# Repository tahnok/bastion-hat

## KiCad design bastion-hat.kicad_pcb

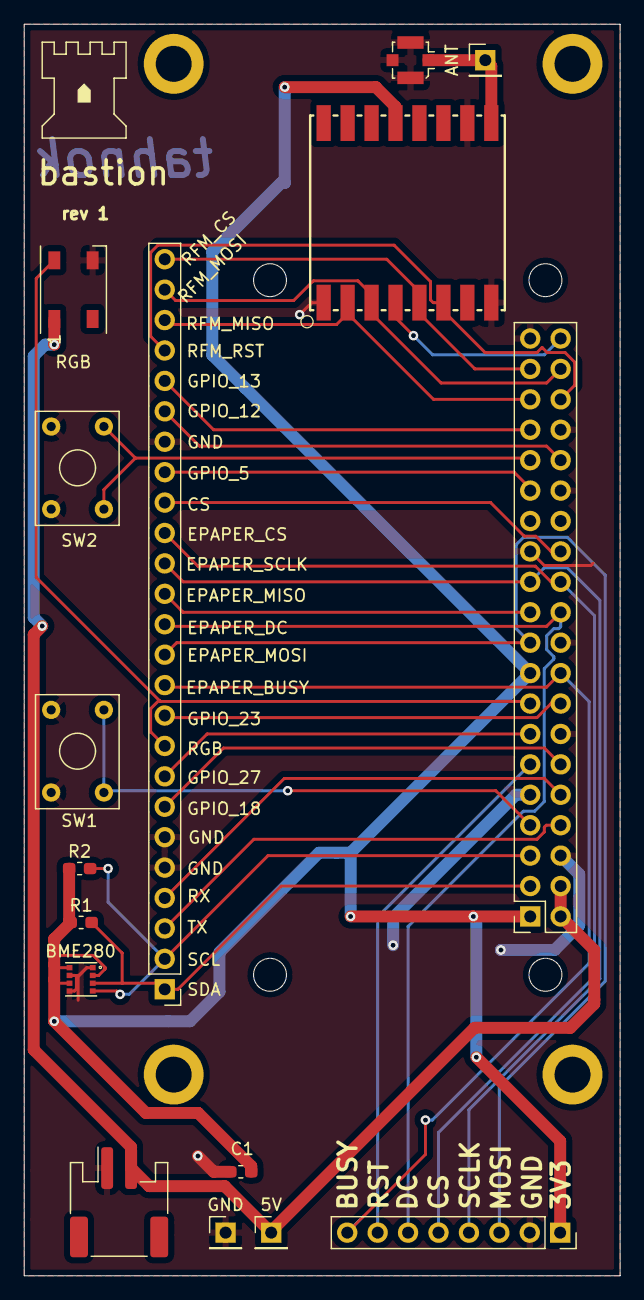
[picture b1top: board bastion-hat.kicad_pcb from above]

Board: 2 copper layers, 49.8 x 104.5 mm, 16 parts (0 on the bottom side), 30 nets.

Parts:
5V: 5V; PinHeader_1x01_P2.54mm_Vertical
ANT: ANT; PinHeader_1x01_P2.54mm_Vertical
BME280: BME280_1; PSON65P250X250X100-8N
C1: 10uF; C_0603_1608Metric_Pad1.05x0.95mm_HandSolder
GND: GND; PinHeader_1x01_P2.54mm_Vertical
J2: Conn_Coaxial; U.FL_Molex_MCRF_73412-0110_Vertical
J3: Raspberry_Pi_2_3; Raspberry_Pi_Zero_Socketed_THT_FaceDown_MountingHoles
J5: JST; JST_PH_S2B-PH-SM4-TB_1x02-1MP_P2.00mm_Horizontal
J7: DEBUG; PinHeader_1x25_P2.54mm_Vertical
R1, R2: 10k; R_0603_1608Metric_Pad1.05x0.95mm_HandSolder
RGB: WS2812B_1; LED_WS2812B_PLCC4_5.0x5.0mm_P3.2mm
SW1, SW2: SW_Push; mini_push_button
U1: RF_Module_RFM95W-915S2; RFM69HCW-XXXS2
U2: waveshare_epaper; PinSocket_1x08_P2.54mm_Vertical

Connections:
+3V3: BME280.2, BME280.6, BME280.8, C1.1, J3.1, J3.17, R1.1, R2.1, U1.13, U2.1
+5V: 5V.1, J3.2, J3.4, J5.2, RGB.1
/CS_1: J3.26, J7.17
/EPAPER_BUSY: J3.18, J7.11, U2.8
/EPAPER_CS: J3.24, J7.16, U2.5
/EPAPER_DC: J3.22, J7.13, U2.6
/EPAPER_MISO: J3.21, J7.14
/EPAPER_MOSI: J3.19, J7.12, U2.3
/EPAPER_RST: J3.11, U2.7
/EPAPER_SCLK: J3.23, J7.15, U2.4
/GPIO5: J3.29, J7.18
/GPIO12: J3.32, J7.20
/GPIO13: J3.33, J7.21
/GPIO18: J3.12, J7.7
/GPIO23: J3.16, J7.10
/GPIO27: J3.13, J7.8
/RFM_ANT: ANT.1, J2.1, U1.9
/RFM_CS: J3.37, J7.25, U1.5
/RFM_MISO: J3.35, J7.23, U1.2
/RFM_MOSI: J3.38, J7.24, U1.3
/RFM_RST: J3.36, J7.22, U1.6
/RFM_SCLK: J3.40, U1.4
/RGB: J3.15, J7.9, RGB.4
/RXD: J3.10, J7.4
/SCL: BME280.4, J3.5, J7.2, R2.2
/SDA: BME280.3, J3.3, J7.1, R1.2
/TXD: J3.8, J7.3
GND: BME280.1, BME280.5, BME280.7, C1.2, GND.1, J2.2, J3.6, J3.9, J3.14, J3.20, J3.25, J3.30, J3.34, J3.39, J5.1, J7.5, J7.6, J7.19, RGB.3, SW1.2, SW2.2, U1.1, U1.8, U1.10, U2.2
unnamed: J3.7, SW1.1
unnamed: J3.31, SW2.1
